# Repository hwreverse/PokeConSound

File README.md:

# PokeConSound
OPL / OPLL* / SID Soundcard Designs for Pocket Computers (ポケコン) (Sharp, Casio, TRS80-M100,...)

<a href="Orig.Designs/">Original Designs I modeled in KiCAD that gave the inspiration</a>

As soon as the function of the original designs is validated (waiting for the Chinese New Year to finish to order the boards..),<br>
I will rework the designs to add buffering, power supply, a stereo system, bigger chips, you name it !

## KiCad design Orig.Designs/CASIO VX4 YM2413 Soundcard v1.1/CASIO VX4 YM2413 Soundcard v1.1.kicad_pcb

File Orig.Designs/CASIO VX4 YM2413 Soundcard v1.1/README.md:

# Casio VX3,VX4 + Z-1 Soundcard

**Make sure that PCBs are fabricated in 0.8mm thickness, otherwise you couldn't fit the PCB in the 2x15 1.27mm Casio Interface Connector**

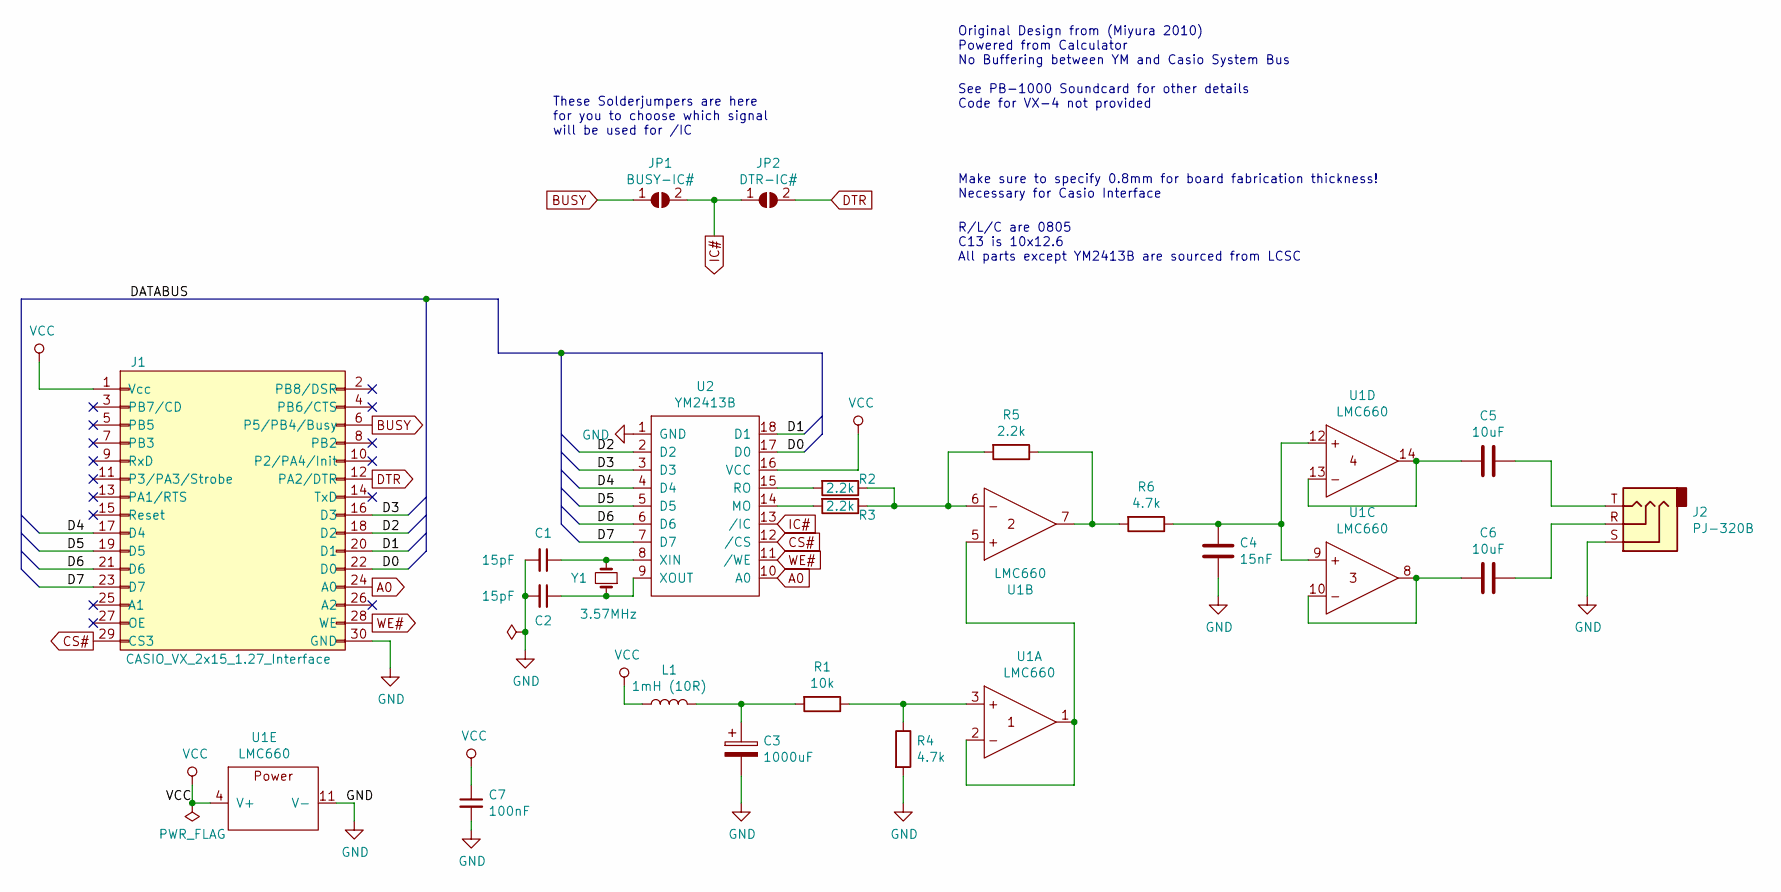
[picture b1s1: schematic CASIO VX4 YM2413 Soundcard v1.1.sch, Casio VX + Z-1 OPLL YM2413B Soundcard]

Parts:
C1, C2: 15pF; C_0805_2012Metric_Pad1.15x1.40mm_HandSolder
C3: 1000uF; CP_Elec_10x12.6
C4: 15nF; C_0805_2012Metric_Pad1.15x1.40mm_HandSolder
C5, C6: 10uF; C_0805_2012Metric_Pad1.15x1.40mm_HandSolder
C7: 100nF; C_0805_2012Metric_Pad1.15x1.40mm_HandSolder
J1: CASIO_VX_2x15_1.27_Interface; Connector_Casio_2x15_1.27_SYSBUS
J2: PJ-320B; BOOMELE_PJ-320B
JP1: BUSY-IC#; SolderJumper-2_P1.3mm_Open_RoundedPad1.0x1.5mm
JP2: DTR-IC#; SolderJumper-2_P1.3mm_Open_RoundedPad1.0x1.5mm
L1: 1mH (10R); L_0805_2012Metric_Pad1.15x1.40mm_HandSolder
R1: 10k; R_0805_2012Metric_Pad1.15x1.40mm_HandSolder
R2, R3, R5: 2.2k; R_0805_2012Metric_Pad1.15x1.40mm_HandSolder
R4, R6: 4.7k; R_0805_2012Metric_Pad1.15x1.40mm_HandSolder
U1: LMC660; SOIC127P600X175-14N
U2: YM2413B; DIP-18_W7.62mm
Y1: 3.57MHz; Crystal_SMD_HC49-SD_HandSoldering

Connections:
/D0: J1.22 (D0), U2.17 (D0)
/D1: J1.20 (D1), U2.18 (D1)
/D2: J1.18 (D2), U2.2 (D2)
/D3: J1.16 (D3), U2.3 (D3)
/D4: J1.17 (D4), U2.4 (D4)
/D5: J1.19 (D5), U2.5 (D5)
/D6: J1.21 (D6), U2.6 (D6)
/D7: J1.23 (D7), U2.7 (D7)
A0: J1.24 (A0), U2.10 (A0)
BUSY: J1.6 (P5/PB4/Busy), JP1.1 (A)
CS#: J1.29 (CS3), U2.12 (/CS)
DTR: J1.12 (PA2/DTR), JP2.2 (B)
GND: C1.2, C2.2, C3.2, C4.2, C7.2, J1.30 (GND), J2.S, R4.2, U1.11 (V-), U2.1 (GND)
IC#: JP1.2 (B), JP2.1 (A), U2.13 (/IC)
unnamed: C1.1, U2.8 (XIN), Y1.2
unnamed: C2.1, U2.9 (XOUT), Y1.1
unnamed: C3.1, L1.2, R1.2
unnamed: C4.1, R6.1, U1.9, U1.12
unnamed: C5.1, U1.13, U1.14
unnamed: C5.2, J2.T
unnamed: C6.1, U1.8, U1.10
unnamed: C6.2, J2.R
unnamed: R1.1, R4.1, U1.3
unnamed: R2.1, R3.1, R5.2, U1.6
unnamed: R2.2, U2.15 (RO)
unnamed: R3.2, U2.14 (MO)
unnamed: R5.1, R6.2, U1.7
unnamed: U1.1, U1.2, U1.5
VCC: C7.1, J1.1 (Vcc), L1.1, U1.4 (V+), U2.16 (VCC)
WE#: J1.28 (WE), U2.11 (/WE)

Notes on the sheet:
Make sure to specify 0.8mm for board fabrication thickness! Necessary for Casio Interface
R/L/C are 0805 C13 is 10x12.6 All parts except YM2413B are sourced from LCSC
Original Design from (Miyura 2010) Powered from Calculator No Buffering between YM and Casio System Bus See PB-1000 Soundcard for other details Code for VX-4 not provided
These Solderjumpers are here for you to choose which signal will be used for /IC

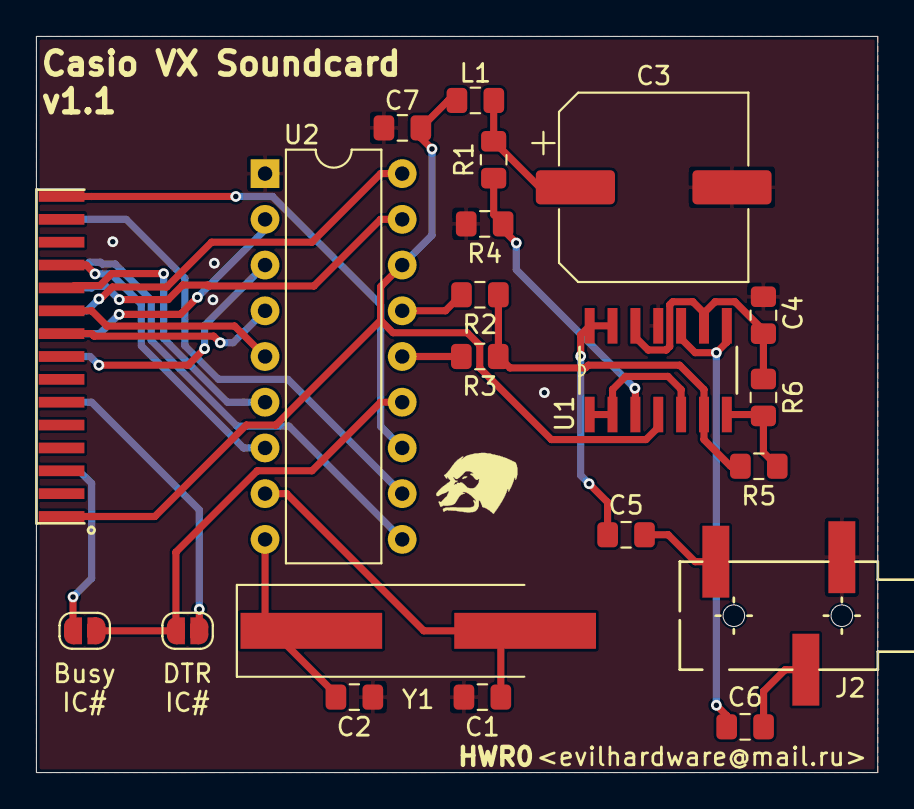
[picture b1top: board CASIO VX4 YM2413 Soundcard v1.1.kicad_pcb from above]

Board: 2 copper layers, 46.7 x 40.9 mm, 21 parts (0 on the bottom side), 30 nets.

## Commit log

2020-01-25 Original designs Upload
2020-01-25 readme links
2020-01-25 added img in root .md
